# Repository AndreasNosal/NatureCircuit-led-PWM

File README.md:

# Mobile-Controlled Light

This project showcases a light fixture that can be controlled remotely via a smartphone (using ESP32 and BLE/Wi-Fi). The device is designed for flexible operation and easy assembly, making it suitable for a wide range of DIY enthusiasts or educational projects. By incorporating a custom PCB, an LED panel, and 3D-printed parts, you can create a smart lighting system that connects seamlessly to your mobile phone.

Originally designed to help users learn about PCB assembly, soldering techniques, and microcontroller programming, this project emphasizes a hands-on approach. Whether you order your PCBs from JLCPCB and print your own stencil for the LED panel or simply 3D-print the housing at home, you’ll gain valuable experience in hardware assembly and coding for an IoT-focused device.

Our webside for instructions: https://nature-circuit.tech/courses

## Features
- **ESP32-Based Controller**: Uses two main files (`main.py` and `ble_advertising.py`) to establish a reliable Bluetooth connection for receiving commands from your smartphone.
- **LED Panel**: Powered by an optional custom PCB or a standard LED strip; easily replaceable or upgradable.
- **3D-Printable Enclosure**: Designed for FDM printing with minimal supports. Can also be adapted to various 3D printers.
- **Scalable Assembly**: Choose between ordering a stencil for solder paste application or printing your own with a standard 3D printer.
- **Easy Soldering**: Ideal for beginners; the main PCB has through-hole or straightforward SMD components, and the layout is beginner-friendly.
- **Flexible Power Input**: Operates on typical USB power or a regulated supply (e.g., 5V).  

## Getting Started
1. **Gather Materials**: Order or produce the main PCB (recommended via JLCPCB) and LED panel. If you own a 3D printer, you can create the stencil for solder paste application.  
2. **Print Enclosure**: Use your preferred 3D printer and slicer settings (e.g., minimal supports). PLA or PETG are commonly used filaments.  
3. **Solder Components**: Prepare your soldering iron (typically 320–350 °C). Follow the silkscreen labels on the PCB and reference any documentation or schematics for correct polarity and placement.  
4. **Program the ESP32**:  
   - Upload `main.py` and `ble_advertising.py` to the ESP32 board.  
   - `main.py` runs automatically on reboot.  
   - `ble_advertising.py` enables BLE connectivity so the device can receive commands.  
5. **Assemble & Power Up**: Once everything is in place, provide power (5V recommended), and check the device’s functionality by connecting with your mobile phone.

## Usage
- **Mobile App Connection**: Use a compatible app (or custom-developed one) to scan and connect via BLE.  
- **Light Control**: Toggle the light on/off or adjust brightness (if supported).  
- **Firmware Updates**: Modify `main.py` for custom behavior, color transitions, scheduling, or advanced IoT integration.

## License
- Under **GPL-3.0** license.

## Example in Action

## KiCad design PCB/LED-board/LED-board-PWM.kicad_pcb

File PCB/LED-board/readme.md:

Board for controlling the led panel.

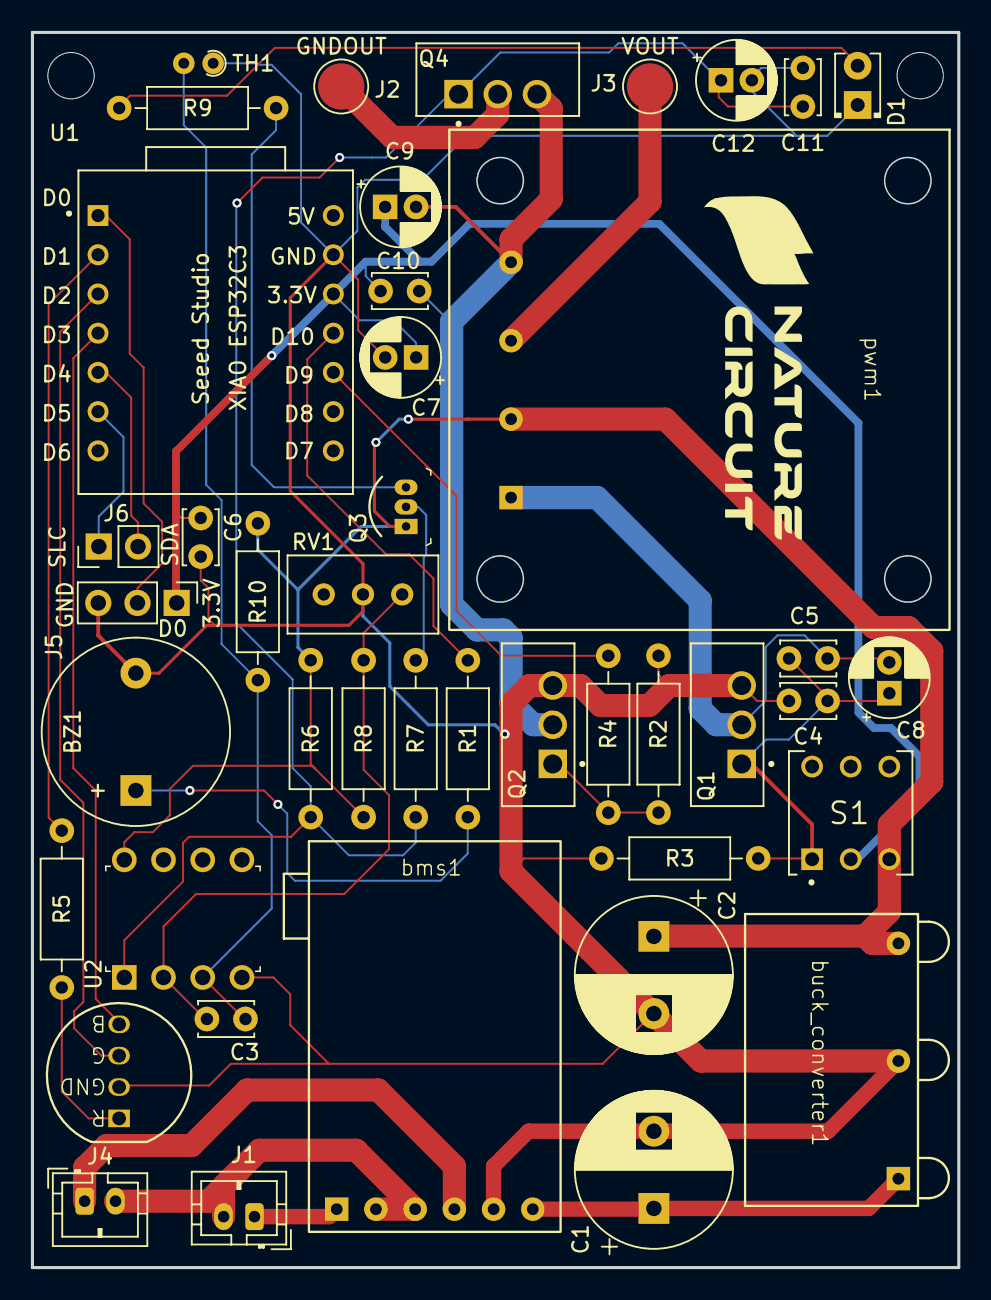
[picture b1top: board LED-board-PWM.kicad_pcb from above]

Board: 2 copper layers, 60.0 x 80.0 mm, 43 parts (0 on the bottom side), 28 nets.

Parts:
BZ1: Buzzer; Buzzer_12x9.5RM7.6
C1, C2: 1000uF; CP_Radial_D10.0mm_P5.00mm
C3, C4, C5, C6, C10, C11: 0.1uF; C_Disc_D3.4mm_W2.1mm_P2.50mm
C7, C8, C9, C12: 47uF; CP_Radial_D5.0mm_P2.00mm
D1: LED; LED_D2.0mm_W4.0mm_H2.8mm_FlatTop
J1, J4: Conn_01x02_Socket; JST_PH_B2B-PH-K_1x02_P2.00mm_Vertical
J2, J3: Conn_01x01_Pin; TestPoint_Pad_D3.0mm
J5: Conn_01x03_Pin; PinHeader_1x03_P2.54mm_Vertical
J6: Conn_01x02_Socket; PinHeader_1x02_P2.54mm_Vertical
LED1: RGB; RGB_LED
Q1, Q2, Q4: IRLZ44N
Q3: 2N3906; TO-92-3
R1: R150; R_Axial_DIN0207_L6.3mm_D2.5mm_P10.16mm_Horizontal
R2, R3, R7: K10; R_Axial_DIN0207_L6.3mm_D2.5mm_P10.16mm_Horizontal
R4: R200; R_Axial_DIN0207_L6.3mm_D2.5mm_P10.16mm_Horizontal
R5: R65; R_Axial_DIN0207_L6.3mm_D2.5mm_P10.16mm_Horizontal
R6: K4.7; R_Axial_DIN0207_L6.3mm_D2.5mm_P10.16mm_Horizontal
R8: K5; R_Axial_DIN0207_L6.3mm_D2.5mm_P10.16mm_Horizontal
R9: R50; R_Axial_DIN0207_L6.3mm_D2.5mm_P10.16mm_Horizontal
R10: K7; R_Axial_DIN0207_L6.3mm_D2.5mm_P10.16mm_Horizontal
RV1: R_Potentiometer_Trim; Potentiometer_Bourns_3296W_Vertical
S1: TL2285EE; SW_TL2285EE
TH1: Thermistor_NTC; R_Axial_DIN0204_L3.6mm_D1.6mm_P1.90mm_Vertical
U1: Seeed_Studio_XIAO_ESP32C3; MODULE_Seeed_Studio_XIAO_ESP32C3
U2: LM393N_LTB; DIP-8_W7.62mm
bms1: MH_CD42_Charge_Discharge_Module
buck_converter1: TZT_4A_Mini_DC_DC_Buck_Converter
pwm1: PWM_regulator_2A

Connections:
BAT: J4.1, bms1.4 (BAT)
D0: J5.2, U1.1 (D0)
ESP32-3.3V: C6.1, C7.1, C9.1, C10.2, J5.1, S1.2, U1.12 (VCC_3V3)
GND: BZ1.2 (-), C1.2, C2.2, C4.2, C6.2, C7.2, C11.2, C12.2, D1.1 (K), J1.2, J4.2, J5.3, LED1.2 (GND), Q1.3, Q2.3, R2.1, R3.1, RV1.2, TH1.1, U1.13 (GND), U2.4 (GND), bms1.2 (GND), bms1.3 (GND), bms1.5 (GND), buck_converter1.2 (GND)
GNDOUT: J2.1, Q4.2
unnamed: BZ1.1 (+), R1.2
unnamed: C3.1, R8.2, RV1.1, U2.2
unnamed: C3.2, R10.1, TH1.2, U2.3
unnamed: C4.1, C5.1, C8.1, Q1.1, R3.2, S1.1
unnamed: C11.1, C12.1, Q4.1, R6.1, R7.1, U2.1
unnamed: D1.2 (A), R9.1
unnamed: LED1.4 (BLUE), U1.4 (D3)
unnamed: LED1.3 (GREEN), U1.3 (D2)
unnamed: LED1.1 (RED), R5.1
unnamed: Q2.1, R2.2, R4.1
unnamed: Q3.2 (B), R7.2
unnamed: Q3.3 (C), R9.2
unnamed: R5.2, U1.2 (D1)
unnamed: R4.2, U1.10 (D9)
unnamed: R1.1, U1.11 (D10)
unnamed: C5.2, C8.2, Q1.2, pwm1.1 (GNDIN)
unnamed: C9.2, C10.1, Q2.2, Q4.3, pwm1.4 (GNDOUT)
SDA: J6.2, U1.5 (D4)
SLC: J6.1, U1.6 (D5)
VIN: J1.1, bms1.1 (VIN)
VOUT: J3.1, pwm1.3 (VOUT)
VOUT-3.3: C2.1, Q3.1 (E), R6.2, R8.1, R10.2, S1.3, U2.8 (VCC), buck_converter1.3 (VOUT), pwm1.2 (VIN)
VOUT-5: C1.1, bms1.6 (VOUT-5V), buck_converter1.1 (VIN)

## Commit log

2025-03-16 Added chematic for led-pwm main board
2025-03-16 Added_main_board_schematic
2025-03-16 Added Kicad files
2025-03-16 Gerber files for production
2025-03-16 Added gerber files for production JLCPCB
2025-03-16 Create LICENSE
2025-03-16 Added files for the led-pwm
2025-03-16 Create 3D_files
2025-03-16 Addded all 3D files
